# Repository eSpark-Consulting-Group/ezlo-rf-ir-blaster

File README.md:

# Scope of Work

1. The first task will be to convert the design from KiCAD into Altium.
2. This will be followed by a review phase where the whole design will be checked thoroughly for any errors or issues or enhancements. This will be done keeping in mind that prototypes of this design are are already tested and working properly.
3. After this, the design will be forwarded to fabrication.

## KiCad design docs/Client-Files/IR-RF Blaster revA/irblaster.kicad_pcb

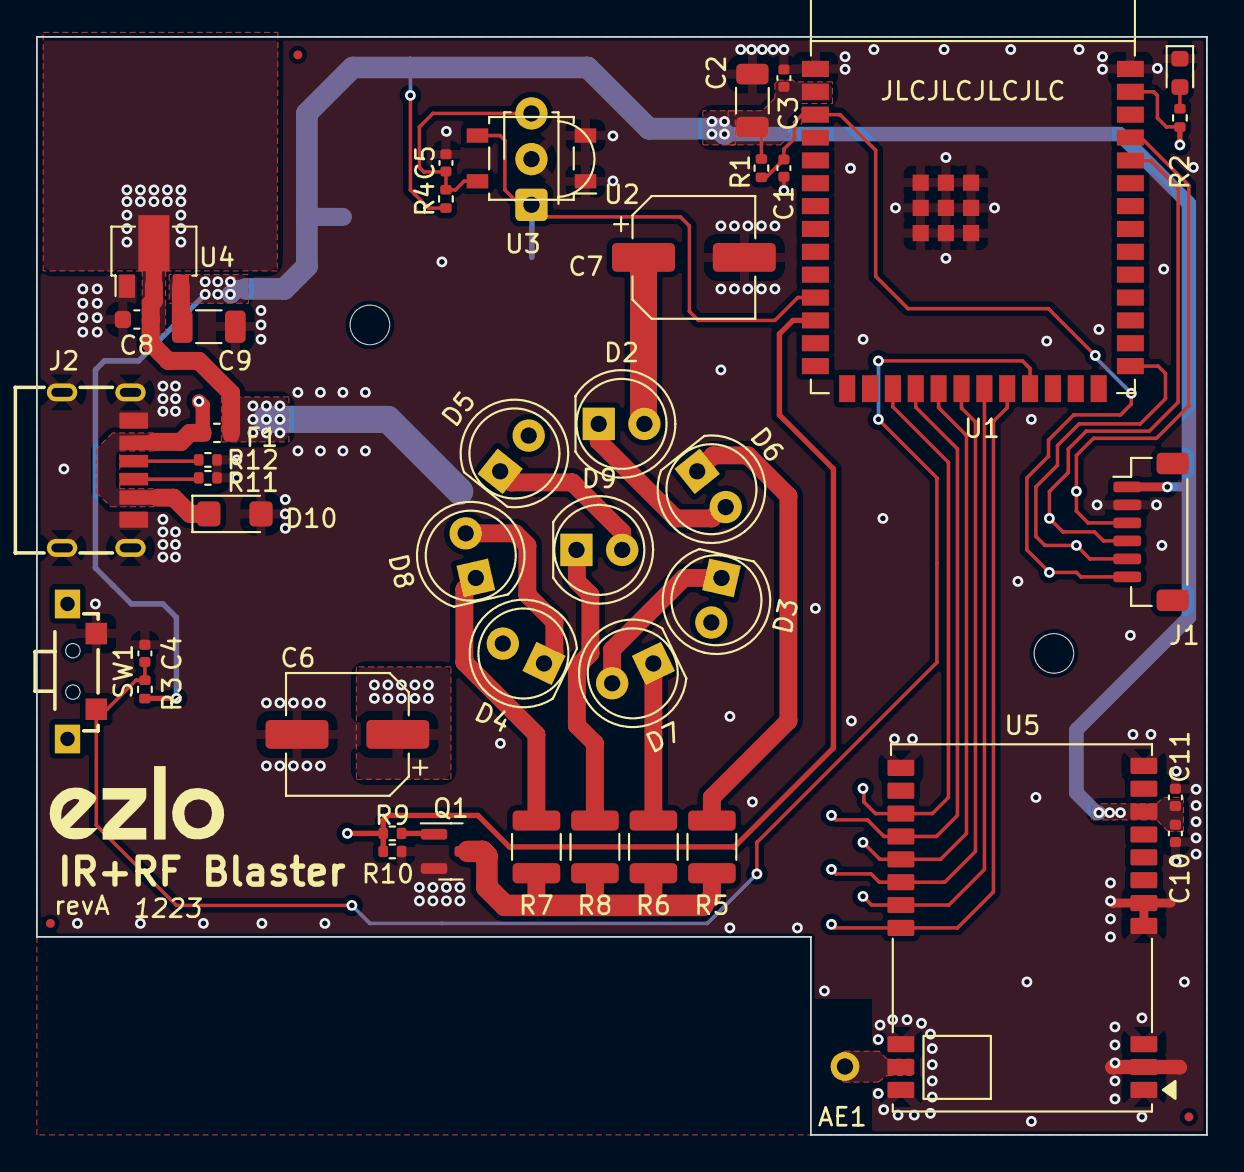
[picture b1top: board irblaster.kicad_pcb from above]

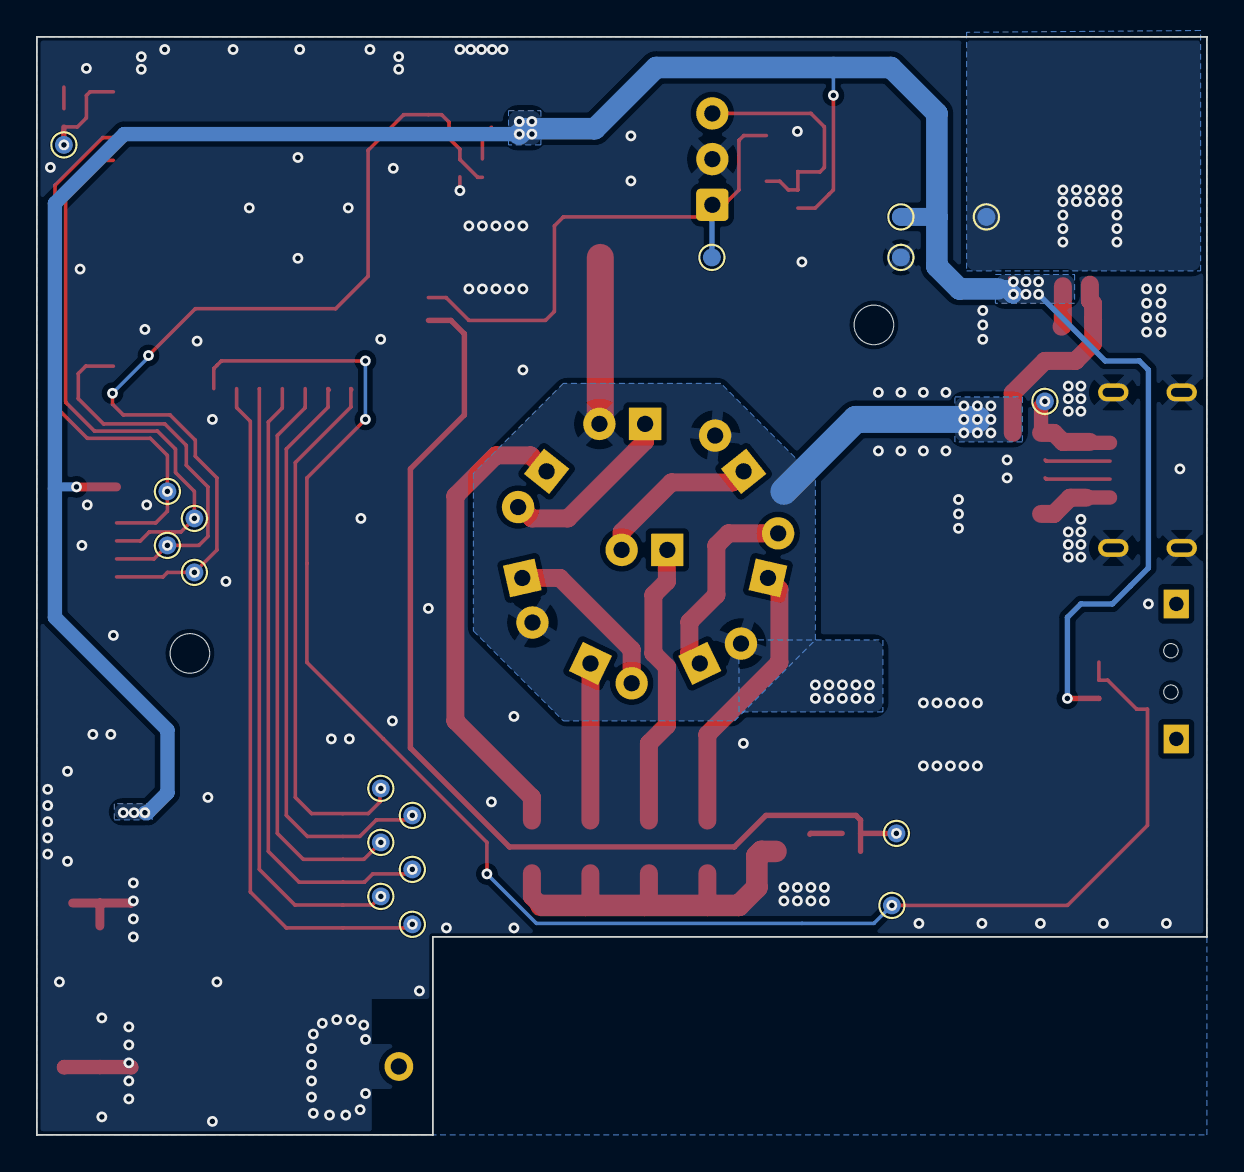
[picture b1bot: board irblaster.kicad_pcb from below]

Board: 2 copper layers, 65.0 x 61.0 mm, 68 parts (18 on the bottom side), 33 nets.

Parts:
AE1: Antenna; RF-433-Helical
C1, C11: 1uF; C_0402_1005Metric
C2, C9: 22uF; C_1206_3216Metric
C3, C4, C10: 0.1uF; C_0402_1005Metric
C5: 4.7uF; C_0402_1005Metric
C6, C7: 220uF; CP_Elec_6.3x5.4
C8: 10uF; C_0603_1608Metric
D1: LED_GREEN; LED_0603_1608Metric
D2, D3, D4, D5, D6, D7, D8, D9: IR333-A; LED_D5.0mm
D10: SMF5.0CA; D_SMF
F1: 1A; Fuse_0603_1608Metric
FID1, FID2, FID3: Fiducial; Fiducial_0.5mm_Mask1mm
H1, H2: MountingHole; MountingHole_2.2mm_M2
J1: VoltLink_target; VoltLink-vertical
J2: TYPE-C-31-M-17
Q1: YJL2302B; SOT-23
R1, R3, R10: 10K; R_0402_1005Metric
R2: 1K; R_0402_1005Metric
R4, R9: 100R; R_0402_1005Metric
R5, R6, R7, R8: 14R; R_1210_3225Metric
R11, R12: 5K1; R_0402_1005Metric
SW1: USER; Switch_YTS-B003-2A
TP1: EN; TestPoint_Pad_D1.0mm
TP2: IO0; TestPoint_Pad_D1.0mm
TP3: RXD; TestPoint_Pad_D1.0mm
TP4: TXD; TestPoint_Pad_D1.0mm
TP5: SWITCH; TestPoint_Pad_D1.0mm
TP6: LED; TestPoint_Pad_D1.0mm
TP7: RX; TestPoint_Pad_D1.0mm
TP8: TX; TestPoint_Pad_D1.0mm
TP9: GND; TestPoint_Pad_D1.0mm
TP10: VBUS; TestPoint_Pad_D1.0mm
TP11: +5V; TestPoint_Pad_D1.0mm
TP12: +3V3; TestPoint_Pad_D1.0mm
TP13: GD02; TestPoint_Pad_D1.0mm
TP14: GD00; TestPoint_Pad_D1.0mm
TP15: MISO; TestPoint_Pad_D1.0mm
TP16: MOSI; TestPoint_Pad_D1.0mm
TP17: SCK; TestPoint_Pad_D1.0mm
TP18: CS; TestPoint_Pad_D1.0mm
U1: ESP32-S3-WROOM-1U-N4; ESP32-S3-WROOM-1
U2: IRM-H638T/TR2; SO-4_4.4x4.3mm_P2.54mm
U3: IRM-3638T; Vishay_MINICAST-3Pin
U4: LR1107; SOT-89-3
U5: E07-400M10S; EBYTE-E07-M10S
V1: EZLO_LOGO; Logo Ezlo_M

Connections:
+3V3: C2.2, C3.2, C9.1, C10.2, C11.1, J1.1 (3V3), R1.2, R3.2, R4.1, TP12.1, U1.2 (3V3), U4.3 (VOUT), U5.9 (VCC)
+5V: C6.1, C7.1, C8.1, D2.2 (A), D3.2 (A), D4.2 (A), D5.2 (A), F1.1, TP11.1, U4.2 (VIN)
/CC1101/ANT_FEED: AE1.1 (A), U5.21 (ANT)
/EN: C1.1, J1.6 (EN), R1.1, TP1.1, U1.3 (EN)
/GPIO1: R2.1, TP6.1, U1.39 (GPIO1)
/GPIO8: R9.2, R10.2, TP8.1, U1.12 (GPIO8)
/GPIO9: TP13.1, U1.17 (GPIO9), U5.14 (GD02)
/GPIO10: TP14.1, U1.18 (GPIO10), U5.15 (GD00)
/GPIO11: TP15.1, U1.19 (GPIO11), U5.16 (MISO/GD01)
/GPIO12: TP16.1, U1.20 (GPIO12), U5.17 (MOSI)
/GPIO13: TP17.1, U1.21 (GPIO13), U5.18 (SCK)
/GPIO14: TP18.1, U1.22 (GPIO14), U5.19 (~CS)
/GPIO18: TP7.1, U1.11 (GPIO18), U2.3 (OUT), U3.1 (OUT)
/GPIO21: C4.1, R3.1, SW1.1, TP5.1, U1.23 (GPIO21)
/IO0: J1.5 (IO0), TP2.1, U1.27 (GPIO0/BOOT)
/RXD: J1.4 (RXD), TP3.1, U1.36 (U0RXD/GPIO44)
/TXD: J1.3 (TXD), TP4.1, U1.37 (U0TXD/GPIO43)
/USB Power/CC1: J2.A5 (CC1), R12.1
/USB Power/CC2: J2.B5 (CC2), R11.1
/USB Power/VBUS: D10.1 (A1), F1.2, J2.A9 (VBUS), J2.B9 (VBUS), TP10.1
GND: C1.2, C2.1, C3.1, C4.2, C5.2, C6.2, C7.2, C8.2, C9.2, C10.1, C11.2, D1.1 (K), D10.2 (A2), J1.2 (GND), J2.A12 (GND), J2.B12 (GND), J2.SH (SHIELD), Q1.2 (S), R10.1, R11.2, R12.2, SW1.2, TP9.1, U1.1 (GND), U1.40 (GND), U1.41 (GND), U2.1 (GND), U2.2 (GND), U3.2 (GND), U4.1 (GND), U5.1 (GND), U5.2 (GND), U5.3 (GND), U5.4 (GND), U5.5 (GND), U5.11 (GND), U5.12 (GND), U5.20 (GND), U5.22 (GND)
unnamed: D1.2 (A), R2.2
unnamed: D2.1 (K), D6.2 (A)
unnamed: D3.1 (K), D7.2 (A)
unnamed: D4.1 (K), D8.2 (A)
unnamed: D5.1 (K), D9.2 (A)
unnamed: D6.1 (K), R5.2
unnamed: D7.1 (K), R6.2
unnamed: D8.1 (K), R7.2
unnamed: D9.1 (K), R8.2
unnamed: Q1.3 (D), R5.1, R6.1, R7.1, R8.1
unnamed: Q1.1 (G), R9.1
unnamed: C5.1, R4.2, U2.4 (Vcc), U3.3 (Vs)

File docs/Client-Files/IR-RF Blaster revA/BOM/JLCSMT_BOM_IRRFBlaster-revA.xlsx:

Comment | Designator | Footprint | LCSC Part #（optional）
Antenna | AE1, | Ezlo:RF-433-Helical | C381188
1uF | C1, C11, | Capacitor_SMD:C_0402_1005Metric | C1592
22uF | C2, C9, | Capacitor_SMD:C_1206_3216Metric | C408152
0.1uF | C3, C4, C10, | Capacitor_SMD:C_0402_1005Metric | C24452
4.7uF | C5, | Capacitor_SMD:C_0402_1005Metric | C1705
220uF | C6, C7, | Capacitor_SMD:CP_Elec_6.3x5.4 | C267466
10uF | C8, | Capacitor_SMD:C_0603_1608Metric | C92487
LED_GREEN | D1, | LED_SMD:LED_0603_1608Metric | C84267
IR333-A | D2, D3, D4, D5, D6, D7, D8, D9, | LED_THT:LED_D5.0mm | C95407
SMF5.0CA | D10, | Diode_SMD:D_SMF | C2980402
1A | F1, | Fuse:Fuse_0603_1608Metric | C2757929
VoltLink_target | J1, | Voltlog:VoltLink-vertical | C145963
TYPE-C-31-M-17 | J2, | Ezlo:TYPE-C-31-M-17 | C283540
YJL2302B | Q1, | Package_TO_SOT_SMD:SOT-23 | C699316
10K | R1, R3, R10, | Resistor_SMD:R_0402_1005Metric | C25804
1K | R2, | Resistor_SMD:R_0402_1005Metric | C11702
100R | R4, R9, | Resistor_SMD:R_0402_1005Metric | C22775
14R | R5, R6, R7, R8, | Resistor_SMD:R_1210_3225Metric | C333127
5K1 | R11, R12, | Resistor_SMD:R_0402_1005Metric | C25905
USER | SW1, | Ezlo:Switch_YTS-B003-2A | C2910695
ESP32-S3-WROOM-1U-N4 | U1, | Espressif:ESP32-S3-WROOM-1 | C2913197
IRM-H638T/TR2 | U2, | Package_SO:SO-4_4.4x4.3mm_P2.54mm | C91447
IRM-3638T | U3, | OptoDevice:Vishay_MINICAST-3Pin | DNP
LR1107 | U4, | Package_TO_SOT_SMD:SOT-89-3 | C171498
E07-400M10S | U5, | Ezlo:EBYTE-E07-M10S | DNP

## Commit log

2023-08-09 ReadMe Updated
2023-08-09 gitignore added
2023-08-09 KiCad Files pushed
2023-08-10 #1 Schematic Design v1.0
    #1 Schematic Design v1.0
2023-08-10 #1 Validated Schematics
    Validated Schematics
2023-08-15 #3 Placement completed, Routing in Progress
2023-08-16 #3 Routing completed no DRC error
2023-08-17 through hole Test point and overlay update
2023-12-06 SR Latch and New Regulator ICs Added
2023-12-20 New LDO Added
2023-12-21 #5 In progress
2023-12-22 Latch IC and the resistor changed
2023-12-22 #5 Routing completed
2023-12-26 #6 Fresh Deliverables generated.
2023-12-29 #4 CD4043BPWR Updated in PCB and Fresh deliverable generated
